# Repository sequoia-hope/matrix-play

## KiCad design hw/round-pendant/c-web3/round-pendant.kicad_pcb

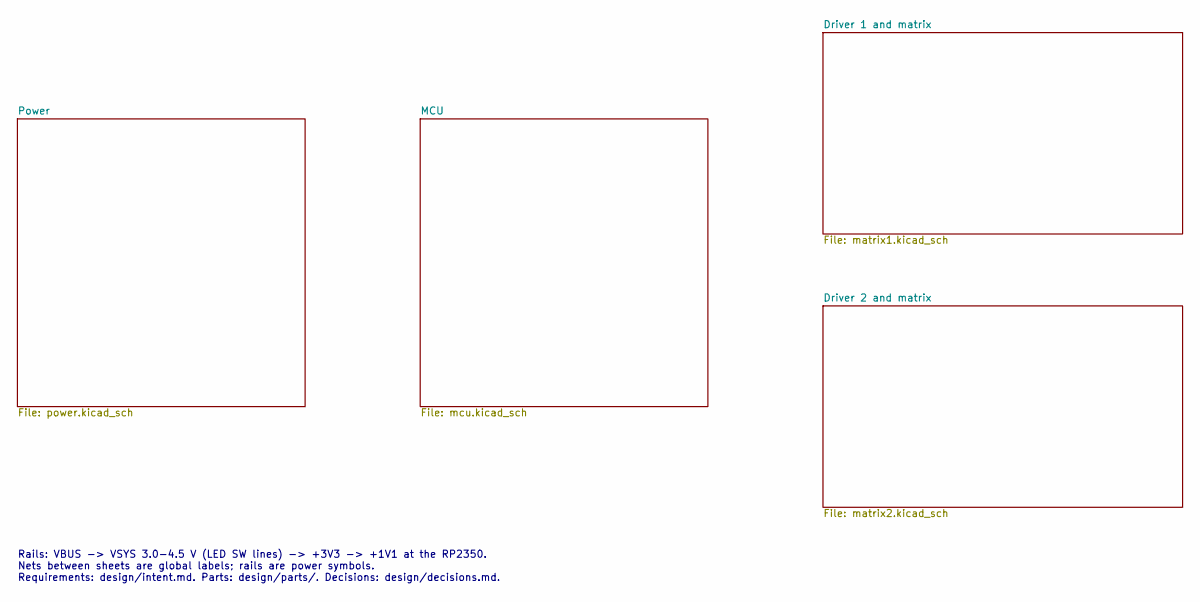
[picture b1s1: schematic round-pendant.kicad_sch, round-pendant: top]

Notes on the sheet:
Rails: VBUS -> VSYS 3.0-4.5 V (LED SW lines) -> +3V3 -> +1V1 at the RP2350. Nets between sheets are global labels; rails are power symbols. Requirements: design/intent.md. Parts: design/parts/. Decisions: design/decisions.md.

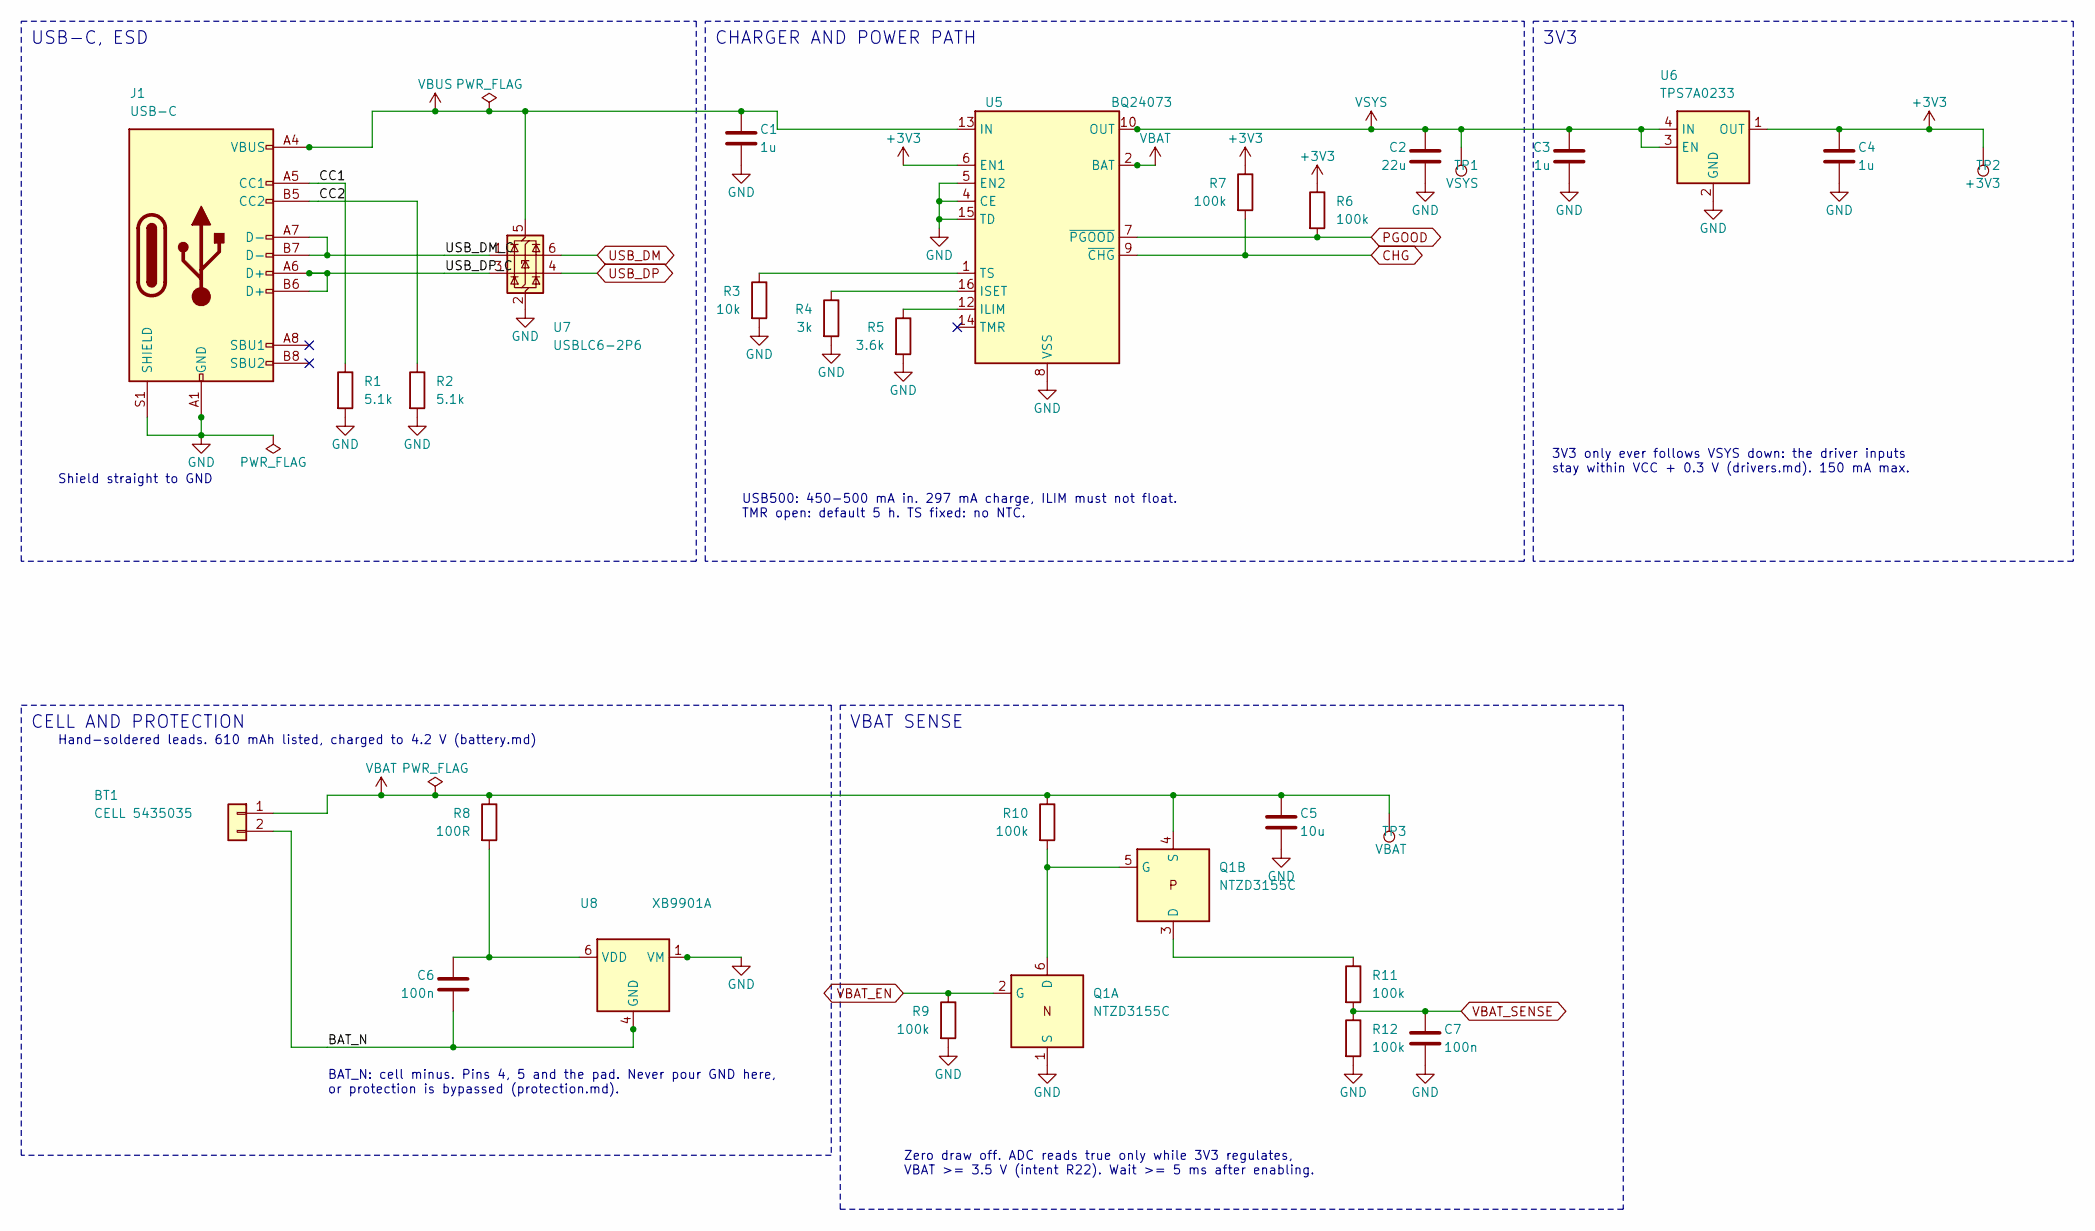
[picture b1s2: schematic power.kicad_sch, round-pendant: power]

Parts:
BT1: CELL 5435035; BatteryPads; MPN 5435035
C1, C3, C4: 1u; C_0402_1005Metric; MPN CL05A105KA5NQNC; LCSC C52923
C2: 22u; C_0603_1608Metric; MPN CL10A226MP8NUNE; LCSC C86295
C5: 10u; C_0603_1608Metric; MPN CL10A106KP8NNNC; LCSC C19702
C6, C7: 100n; C_0402_1005Metric; MPN CL05B104KO5NNNC; LCSC C1525
J1: USB-C; USB_C_Receptacle_HRO_TYPE-C-31-M-12; MPN TYPE-C-31-M-12; LCSC C165948
Q1: NTZD3155C; SOT-563; MPN NTZD3155CT1G; LCSC C236117
R1, R2: 5.1k; R_0402_1005Metric; MPN 0402WGF5101TCE; LCSC C25905
R3: 10k; R_0402_1005Metric; MPN 0402WGF1002TCE; LCSC C25744
R4: 3k; R_0402_1005Metric; MPN 0402WGF3001TCE; LCSC C25784
R5: 3.6k; R_0402_1005Metric; MPN 0402WGF3601TCE; LCSC C25891
R6, R7, R9, R10, R11, R12: 100k; R_0402_1005Metric; MPN 0402WGF1003TCE; LCSC C25741
R8: 100R; R_0402_1005Metric; MPN 0402WGF1000TCE; LCSC C25076
TP1: VSYS; TestPoint_Pad_D1.0mm
TP2: +3V3; TestPoint_Pad_D1.0mm
TP3: VBAT; TestPoint_Pad_D1.0mm
U5: BQ24073; QFN-16-1EP_3x3mm_P0.5mm_EP1.7x1.7mm; MPN BQ24073RGTR; LCSC C15220
U6: TPS7A0233; Texas_X2SON-4_1x1mm_P0.65mm; MPN TPS7A0233PDQNR; LCSC C2860046
U7: USBLC6-2P6; SOT-666; MPN USBLC6-2P6; LCSC C15999
U8: XB9901A; XySemi_DFN-6_1.8x1.4mm; MPN XB9901A; LCSC C669687

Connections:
+3V3: C4.1, R6.1, R7.1, TP2.1, U5.6 (EN1), U6.1 (OUT); also elsewhere on the board
/Power/BAT_N: BT1.2, C6.2, U8.4 (GND), U8.5 (GND)
/Power/CC1: J1.1, J1.A5 (CC1), R1.1
/Power/CC2: J1.2, J1.B5 (CC2), R2.1
/Power/USB_DM_C: J1.3, J1.A7 (D-), J1.B7 (D-), U7.1 (I/O1)
/Power/USB_DP_C: J1.4, J1.A6 (D+), J1.B6 (D+), U7.3 (I/O2)
CHG: R7.2, U5.9 (~CHG); also elsewhere on the board
unnamed: Q1.5 (G), Q1.6 (D), R10.2
unnamed: Q1.3 (D), R11.1
unnamed: R5.1, U5.12 (ILIM)
unnamed: R4.1, U5.16 (ISET)
unnamed: R3.1, U5.1 (TS)
unnamed: C6.1, R8.2, U8.6 (VDD)
PGOOD: R6.2, U5.7 (~PGOOD); also elsewhere on the board
USB_DM: U7.6 (I/O1); also elsewhere on the board
USB_DP: U7.4 (I/O2); also elsewhere on the board
VBAT_EN: Q1.2 (G), R9.1; also elsewhere on the board
VBAT_SENSE: C7.1, R11.2, R12.1; also elsewhere on the board
VSYS: C2.1, C3.1, TP1.1, U5.10 (OUT), U5.11 (OUT), U6.3 (EN), U6.4 (IN); also elsewhere on the board

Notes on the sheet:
Shield straight to GND
USB-C, ESD
USB500: 450-500 mA in. 297 mA charge, ILIM must not float. TMR open: default 5 h. TS fixed: no NTC.
CHARGER AND POWER PATH
3V3 only ever follows VSYS down: the driver inputs stay within VCC + 0.3 V (drivers.md). 150 mA max.
3V3
Hand-soldered leads. 610 mAh listed, charged to 4.2 V (battery.md)
BAT_N: cell minus. Pins 4, 5 and the pad. Never pour GND here, or protection is bypassed (protection.md).
CELL AND PROTECTION
Zero draw off. ADC reads true only while 3V3 regulates, VBAT >= 3.5 V (intent R22). Wait >= 5 ms after enabling.
VBAT SENSE

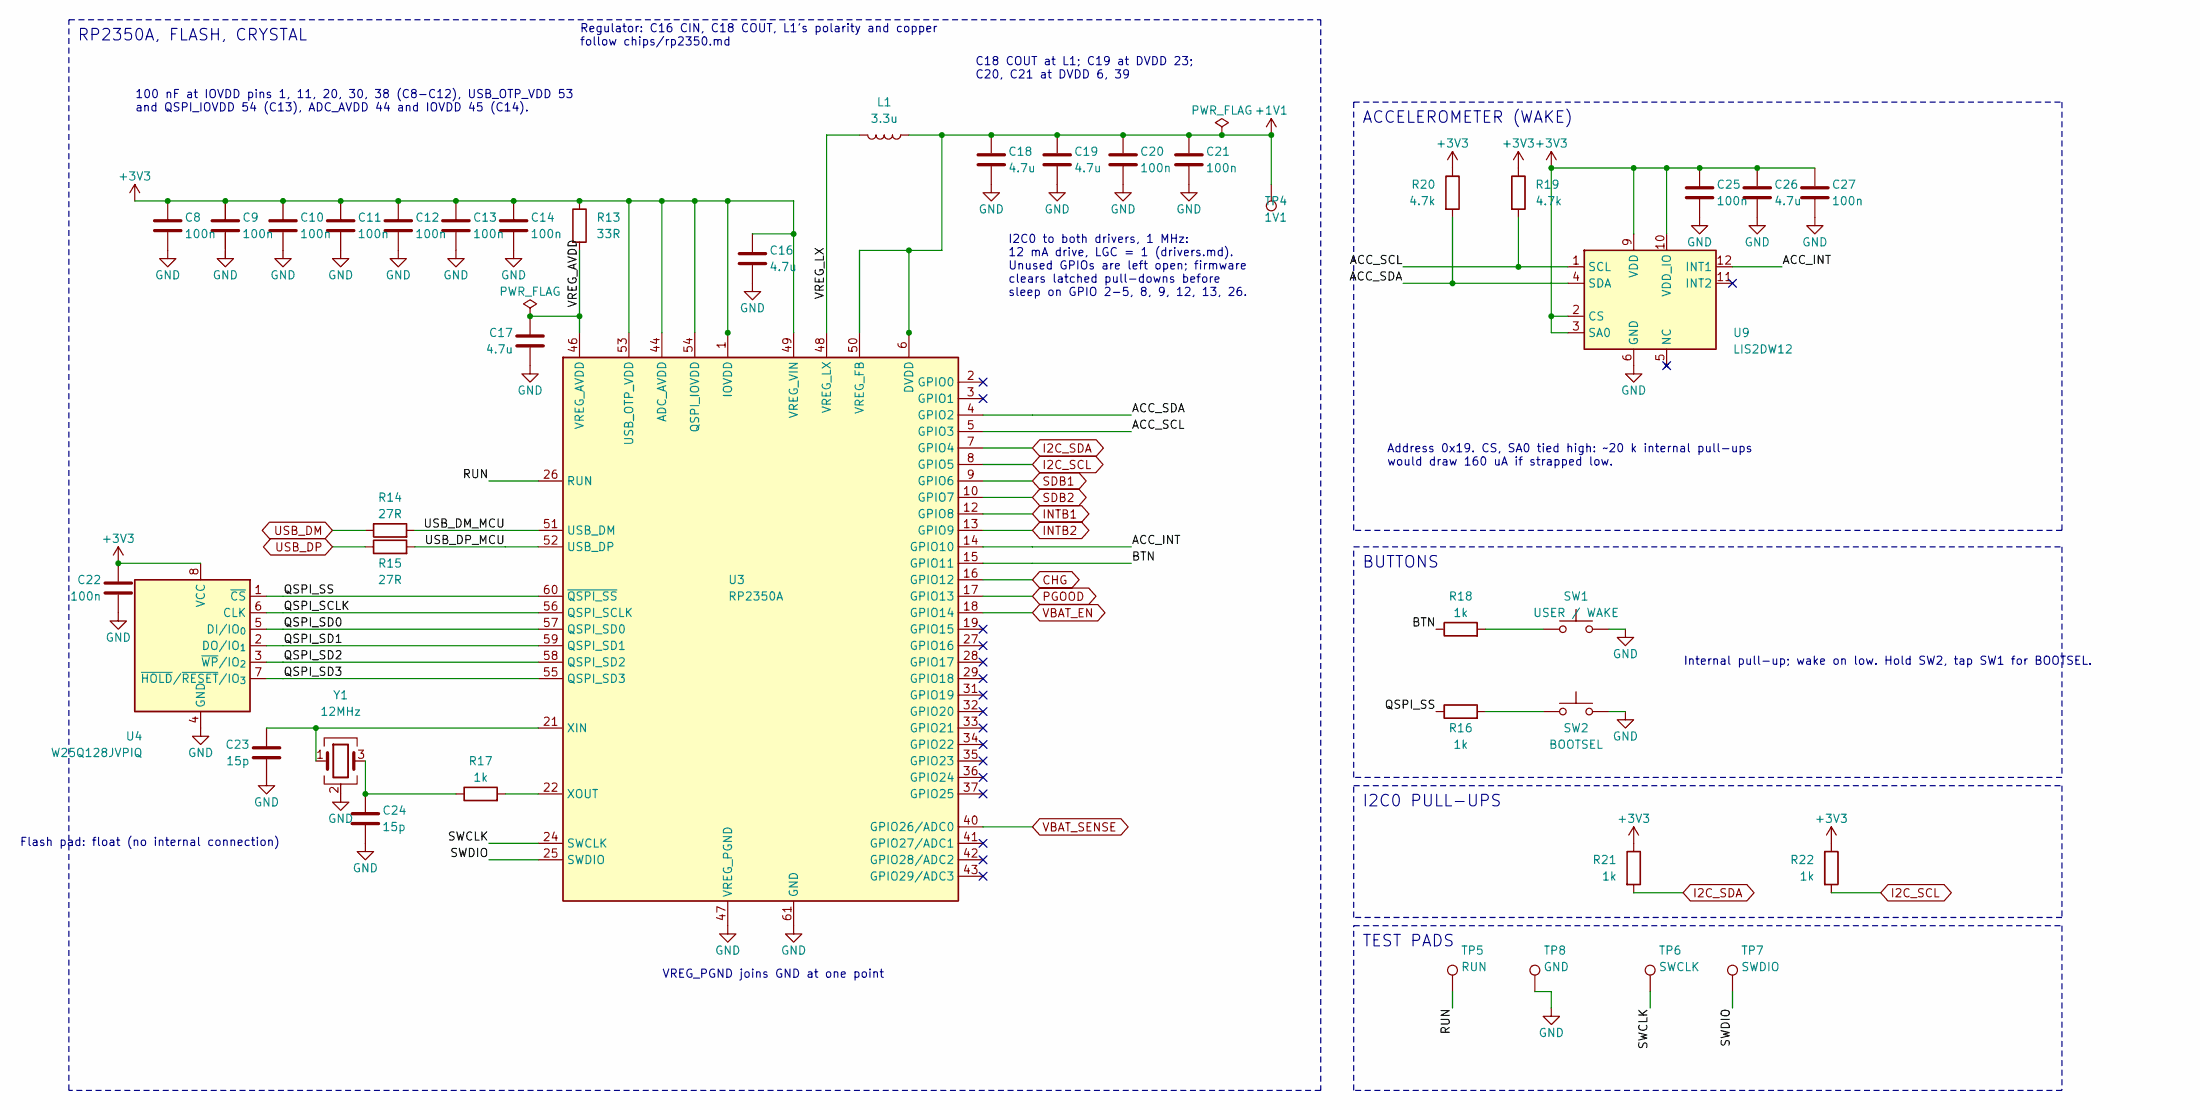
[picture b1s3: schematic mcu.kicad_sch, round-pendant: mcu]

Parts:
C8, C9, C10, C11, C12, C13, C14, C20, C21, C22, C25, C27: 100n; C_0402_1005Metric; MPN CL05B104KO5NNNC; LCSC C1525
C16, C18: 4.7u; C_0402_1005Metric_small_pads; MPN CL05A475MP5NRNC; LCSC C23733
C17, C19, C26: 4.7u; C_0402_1005Metric; MPN CL05A475MP5NRNC; LCSC C23733
C23, C24: 15p; C_0402_1005Metric; MPN 0402CG150J500NT; LCSC C1548
L1: 3.3u; L_pol_2016; MPN AOTA-B201610S3R3-101-T; LCSC C42411119
R13: 33R; R_0402_1005Metric; MPN 0402WGF330JTCE; LCSC C25105
R14, R15: 27R; R_0402_1005Metric; MPN 0402WGF270JTCE; LCSC C25100
R16, R17, R18, R21, R22: 1k; R_0402_1005Metric; MPN 0402WGF1001TCE; LCSC C11702
R19, R20: 4.7k; R_0402_1005Metric; MPN 0402WGF4701TCE; LCSC C25900
SW1: USER / WAKE; SW_Push_1P1T-MP_NO_Horizontal_Alps_SKRTLAE010; MPN SKRTLAE010; LCSC C110293
SW2: BOOTSEL; SW_Push_1P1T-MP_NO_Horizontal_Alps_SKRTLAE010; MPN SKRTLAE010; LCSC C110293
TP4: 1V1; TestPoint_Pad_D1.0mm
TP5: RUN; TestPoint_Pad_D1.0mm
TP6: SWCLK; TestPoint_Pad_D1.0mm
TP7: SWDIO; TestPoint_Pad_D1.0mm
TP8: GND; TestPoint_Pad_D1.0mm
U3: RP2350A; RP2350-QFN-60-1EP_7x7_P0.4mm_EP3.4x3.4mm_ThermalVias; MPN RP2350A; LCSC C42411118
U4: W25Q128JVPIQ; WSON-8_6x5mm_P1.27mm_NoEPCopper; MPN W25Q128JVPIQ; LCSC C190862
U9: LIS2DW12; LGA-12_2x2mm_P0.5mm; MPN LIS2DW12TR; LCSC C189624
Y1: 12MHz; Crystal_SMD_3225-4Pin_3.2x2.5mm; MPN ABM8-272-T3; LCSC C20625731

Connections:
+3V3: C8.1, C9.1, C10.1, C11.1, C12.1, C13.1, C14.1, C16.1, C22.1, C25.1, C26.1, C27.1, R13.1, R19.1, R20.1, R21.1, R22.1, U3.1 (IOVDD), U3.11 (IOVDD), U3.20 (IOVDD), U3.30 (IOVDD), U3.38 (IOVDD), U3.44 (ADC_AVDD), U3.45 (IOVDD), U3.49 (VREG_VIN), U3.53 (USB_OTP_VDD), U3.54 (QSPI_IOVDD), U4.8 (VCC), U9.2 (CS), U9.3 (SA0), U9.9 (VDD), U9.10 (VDD_IO); also elsewhere on the board
/MCU/ACC_INT: U3.14 (GPIO10), U9.12 (INT1)
/MCU/ACC_SCL: R19.2, U3.5 (GPIO3), U9.1 (SCL)
/MCU/ACC_SDA: R20.2, U3.4 (GPIO2), U9.4 (SDA)
/MCU/BTN: R18.1, U3.15 (GPIO11)
/MCU/CLED_B: U3.37 (GPIO25); also elsewhere on the board
/MCU/CLED_G: U3.36 (GPIO24); also elsewhere on the board
/MCU/CLED_R: U3.35 (GPIO23); also elsewhere on the board
/MCU/QSPI_SCLK: U3.56 (QSPI_SCLK), U4.6 (CLK)
/MCU/QSPI_SD0: U3.57 (QSPI_SD0), U4.5 (DI/IO_{0})
/MCU/QSPI_SD1: U3.59 (QSPI_SD1), U4.2 (DO/IO_{1})
/MCU/QSPI_SD2: U3.58 (QSPI_SD2), U4.3 (~WP/IO_{2})
/MCU/QSPI_SD3: U3.55 (QSPI_SD3), U4.7 (~HOLD/~RESET/IO_{3})
/MCU/QSPI_SS: R16.1, U3.60 (~QSPI_SS), U4.1 (~CS)
/MCU/RUN: TP5.1, U3.26 (RUN)
/MCU/SWCLK: TP6.1, U3.24 (SWCLK)
/MCU/SWDIO: TP7.1, U3.25 (SWDIO)
/MCU/USB_DM_MCU: R14.2, U3.51 (USB_DM)
/MCU/USB_DP_MCU: R15.2, U3.52 (USB_DP)
/MCU/VREG_LX: L1.2, U3.48 (VREG_LX)
CHG: U3.16 (GPIO12); also elsewhere on the board
I2C_SCL: R22.2, U3.8 (GPIO5); also elsewhere on the board
I2C_SDA: R21.2, U3.7 (GPIO4); also elsewhere on the board
INTB1: U3.12 (GPIO8); also elsewhere on the board
INTB2: U3.13 (GPIO9); also elsewhere on the board
unnamed: C24.1, R17.1, Y1.3
unnamed: R16.2, SW2.1
unnamed: R18.2, SW1.1
unnamed: C23.1, U3.21 (XIN), Y1.1
unnamed: R17.2, U3.22 (XOUT)
PGOOD: U3.17 (GPIO13); also elsewhere on the board
SDB1: U3.9 (GPIO6); also elsewhere on the board
SDB2: U3.10 (GPIO7); also elsewhere on the board
USB_DM: R14.1; also elsewhere on the board
USB_DP: R15.1; also elsewhere on the board
VBAT_EN: U3.18 (GPIO14); also elsewhere on the board
VBAT_SENSE: U3.40 (GPIO26/ADC0); also elsewhere on the board

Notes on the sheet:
100 nF at IOVDD pins 1, 11, 20, 30, 38 (C8-C12), USB_OTP_VDD 53 and QSPI_IOVDD 54 (C13), ADC_AVDD 44 and IOVDD 45 (C14).
C18 COUT at L1; C19 at DVDD 23; C20, C21 at DVDD 6, 39
Regulator: C16 CIN, C18 COUT, L1's polarity and copper follow chips/rp2350.md
VREG_PGND joins GND at one point
I2C0 to both drivers, 1 MHz: 12 mA drive, LGC = 1 (drivers.md). Unused GPIOs are left open; firmware clears latched pull-downs before sleep on GPIO 2-5, 8, 9, 12, 13, 26.
Flash pad: float (no internal connection)
RP2350A, FLASH, CRYSTAL
Address 0x19. CS, SA0 tied high: ~20 k internal pull-ups would draw 160 uA if strapped low.
ACCELEROMETER (WAKE)
Internal pull-up; wake on low. Hold SW2, tap SW1 for BOOTSEL.
BUTTONS
TEST PADS
I2C0 PULL-UPS

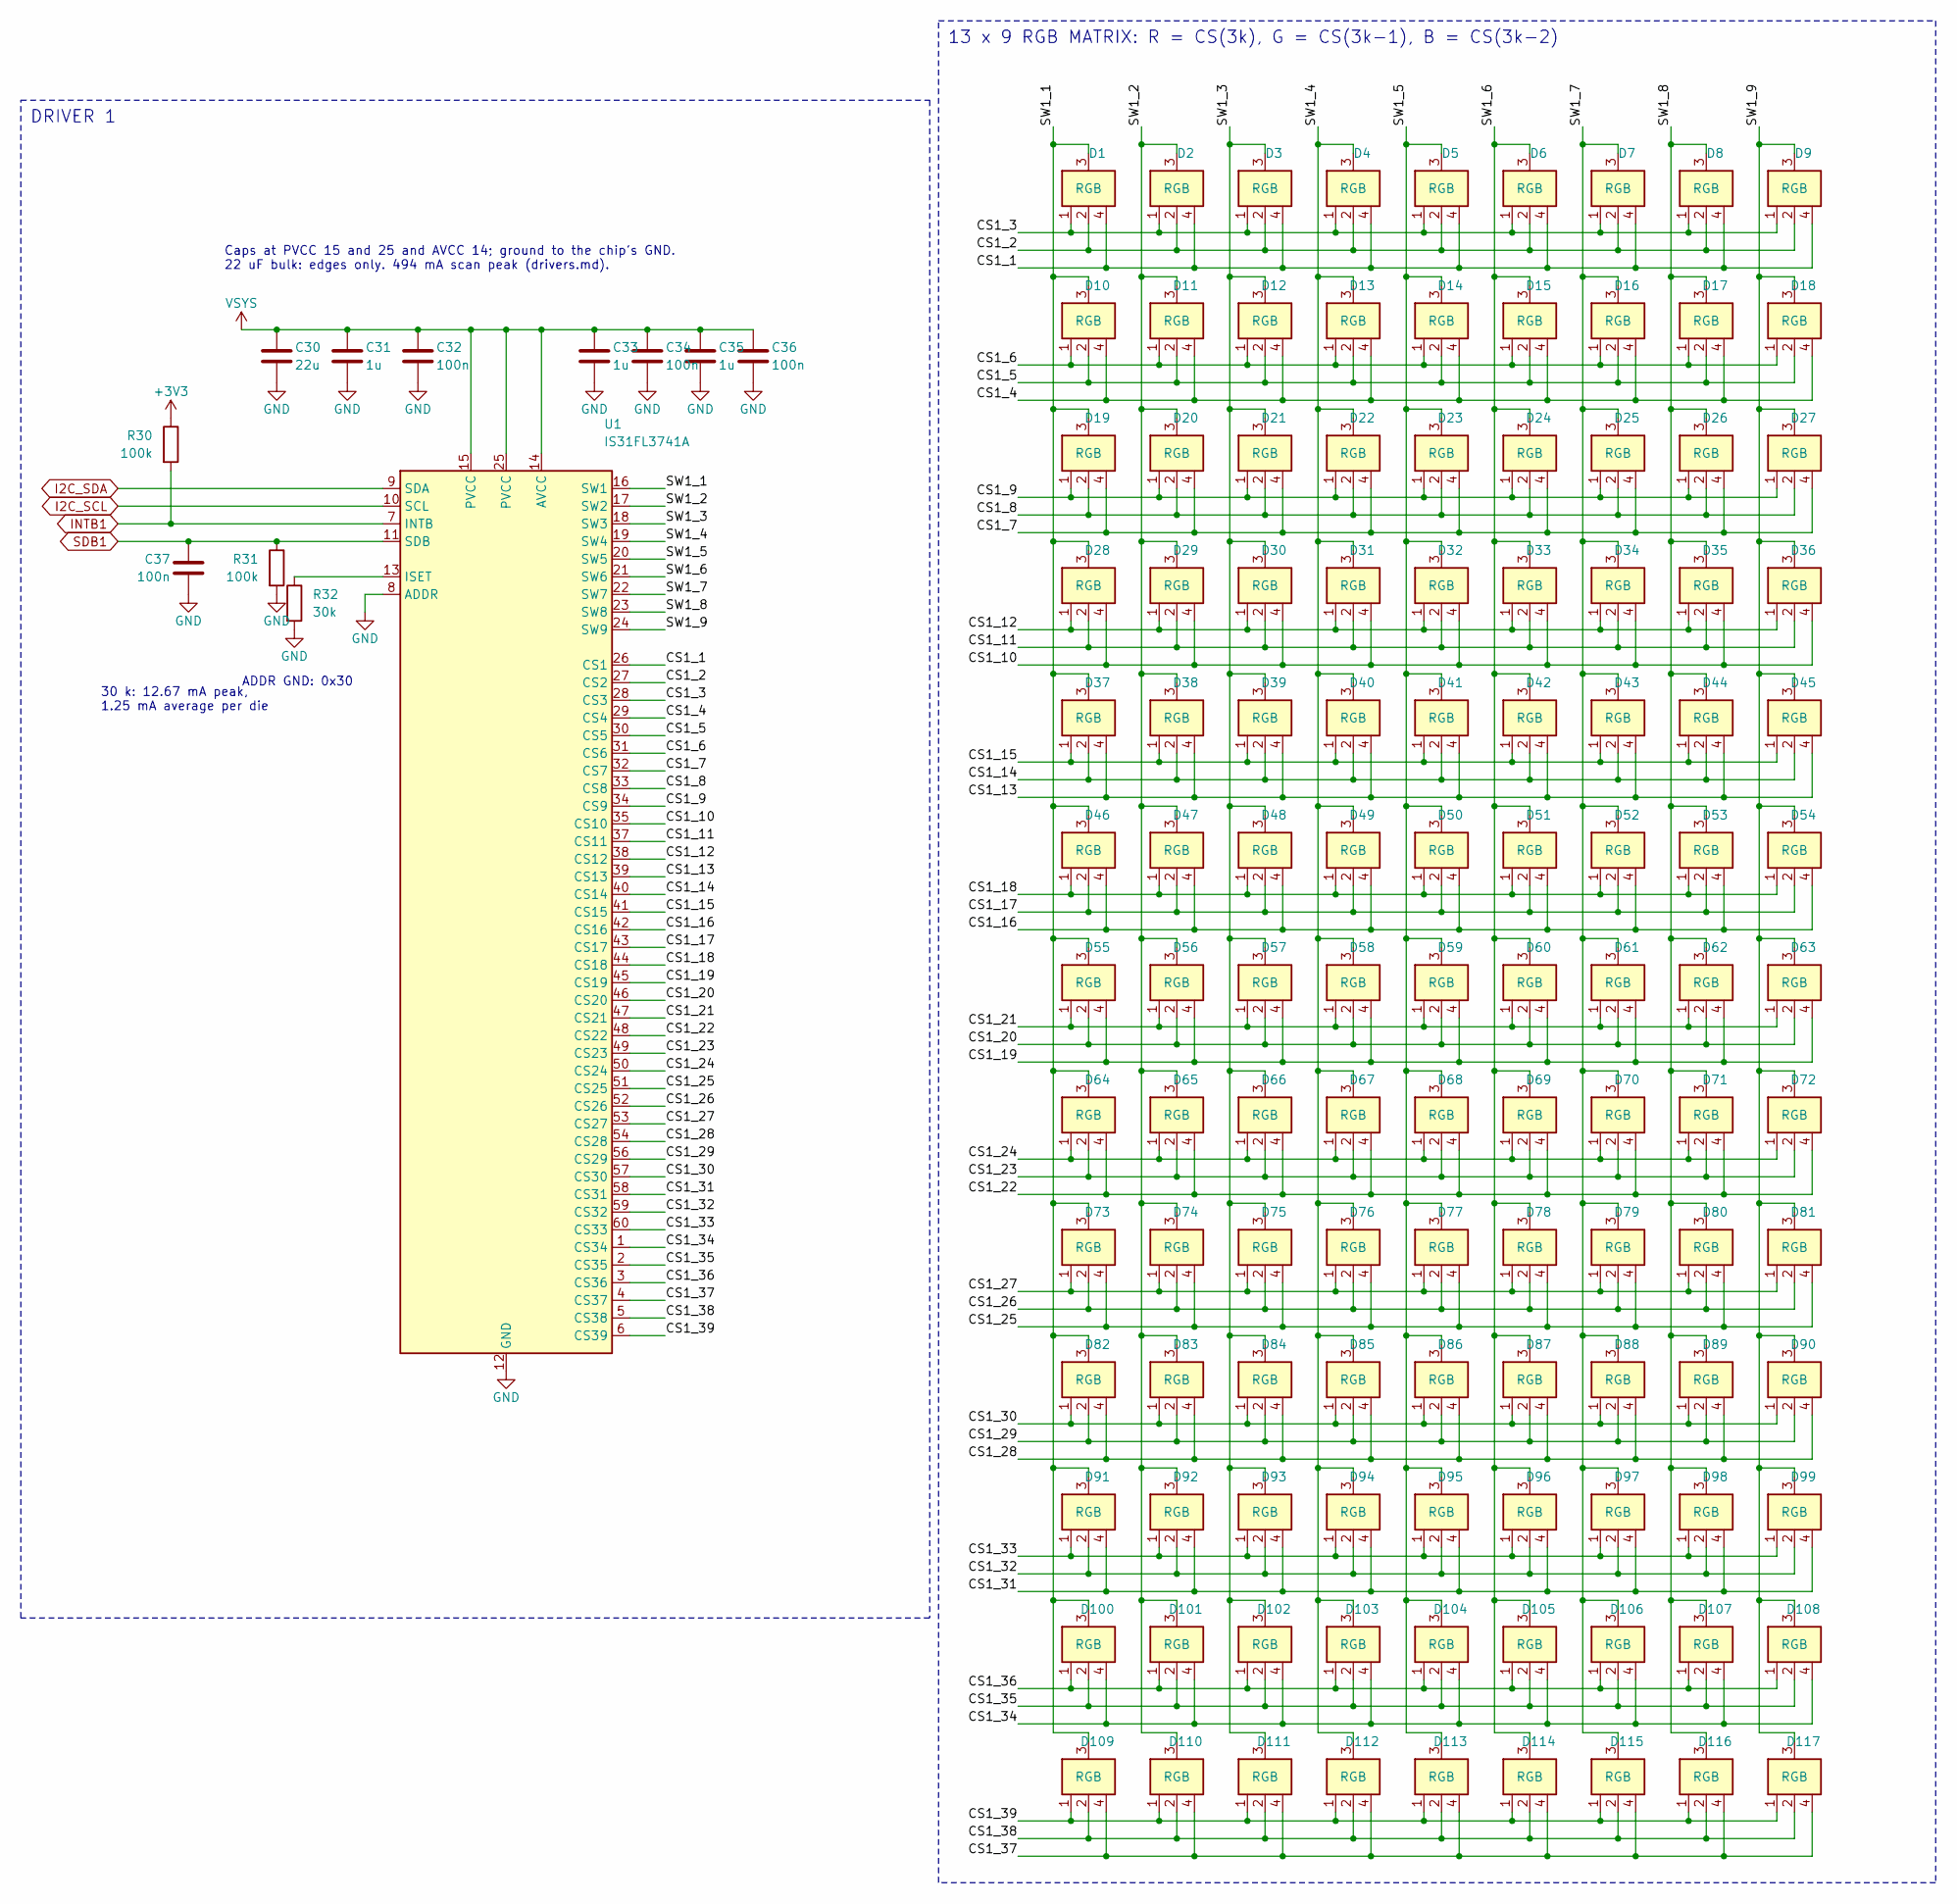
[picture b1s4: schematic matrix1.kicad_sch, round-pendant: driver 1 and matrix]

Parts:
C30: 22u; C_0603_1608Metric; MPN CL10A226MP8NUNE; LCSC C86295
C31, C33, C35: 1u; C_0402_1005Metric; MPN CL05A105KA5NQNC; LCSC C52923
C32, C34, C36, C37: 100n; C_0402_1005Metric; MPN CL05B104KO5NNNC; LCSC C1525
D1, D2, D3, D4, D5, D6, D7, D8, D9, D10, D11, D12, D13, D14, D15, D16, D17, D18, D19, D20, D21, D22, D23, D24, D25, D26, D27, D28, D29, D30, D31, D32, D33, D34, D35, D36, D37, D38, D39, D40, D41, D42, D43, D44, D45, D46, D47, D48, D49, D50, D51, D52, D53, D54, D55, D56, D57, D58, D59, D60, D61, D62, D63, D64, D65, D66, D67, D68, D69, D70, D71, D72, D73, D74, D75, D76, D77, D78, D79, D80, D81, D82, D83, D84, D85, D86, D87, D88, D89, D90, D91, D92, D93, D94, D95, D96, D97, D98, D99, D100, D101, D102, D103, D104, D105, D106, D107, D108, D109, D110, D111, D112, D113, D114, D115, D116, D117: RGB; LED_XL-1010RGB; MPN XL-1010RGB-YG; LCSC C965834
R30, R31: 100k; R_0402_1005Metric; MPN 0402WGF1003TCE; LCSC C25741
R32: 30k; R_0402_1005Metric; MPN 0402WGF3002TCE; LCSC C25776
U1: IS31FL3741A; QFN-60-1EP_7x7mm_P0.4mm_EP5.4x5.4mm; MPN IS31FL3741A-QFLS4-TR; LCSC C2940604

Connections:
+3V3: R30.1; also elsewhere on the board
/Driver 1 and matrix/CS1_1: D1.4 (B), D2.4 (B), D3.4 (B), D4.4 (B), D5.4 (B), D6.4 (B), D7.4 (B), D8.4 (B), D9.4 (B), U1.26 (CS1)
/Driver 1 and matrix/CS1_2: D1.2 (G), D2.2 (G), D3.2 (G), D4.2 (G), D5.2 (G), D6.2 (G), D7.2 (G), D8.2 (G), D9.2 (G), U1.27 (CS2)
/Driver 1 and matrix/CS1_3: D1.1 (R), D2.1 (R), D3.1 (R), D4.1 (R), D5.1 (R), D6.1 (R), D7.1 (R), D8.1 (R), D9.1 (R), U1.28 (CS3)
/Driver 1 and matrix/CS1_4: D10.4 (B), D11.4 (B), D12.4 (B), D13.4 (B), D14.4 (B), D15.4 (B), D16.4 (B), D17.4 (B), D18.4 (B), U1.29 (CS4)
/Driver 1 and matrix/CS1_5: D10.2 (G), D11.2 (G), D12.2 (G), D13.2 (G), D14.2 (G), D15.2 (G), D16.2 (G), D17.2 (G), D18.2 (G), U1.30 (CS5)
/Driver 1 and matrix/CS1_6: D10.1 (R), D11.1 (R), D12.1 (R), D13.1 (R), D14.1 (R), D15.1 (R), D16.1 (R), D17.1 (R), D18.1 (R), U1.31 (CS6)
/Driver 1 and matrix/CS1_7: D19.4 (B), D20.4 (B), D21.4 (B), D22.4 (B), D23.4 (B), D24.4 (B), D25.4 (B), D26.4 (B), D27.4 (B), U1.32 (CS7)
/Driver 1 and matrix/CS1_8: D19.2 (G), D20.2 (G), D21.2 (G), D22.2 (G), D23.2 (G), D24.2 (G), D25.2 (G), D26.2 (G), D27.2 (G), U1.33 (CS8)
/Driver 1 and matrix/CS1_9: D19.1 (R), D20.1 (R), D21.1 (R), D22.1 (R), D23.1 (R), D24.1 (R), D25.1 (R), D26.1 (R), D27.1 (R), U1.34 (CS9)
/Driver 1 and matrix/CS1_10: D28.4 (B), D29.4 (B), D30.4 (B), D31.4 (B), D32.4 (B), D33.4 (B), D34.4 (B), D35.4 (B), D36.4 (B), U1.35 (CS10)
/Driver 1 and matrix/CS1_11: D28.2 (G), D29.2 (G), D30.2 (G), D31.2 (G), D32.2 (G), D33.2 (G), D34.2 (G), D35.2 (G), D36.2 (G), U1.37 (CS11)
/Driver 1 and matrix/CS1_12: D28.1 (R), D29.1 (R), D30.1 (R), D31.1 (R), D32.1 (R), D33.1 (R), D34.1 (R), D35.1 (R), D36.1 (R), U1.38 (CS12)
/Driver 1 and matrix/CS1_13: D37.4 (B), D38.4 (B), D39.4 (B), D40.4 (B), D41.4 (B), D42.4 (B), D43.4 (B), D44.4 (B), D45.4 (B), U1.39 (CS13)
/Driver 1 and matrix/CS1_14: D37.2 (G), D38.2 (G), D39.2 (G), D40.2 (G), D41.2 (G), D42.2 (G), D43.2 (G), D44.2 (G), D45.2 (G), U1.40 (CS14)
/Driver 1 and matrix/CS1_15: D37.1 (R), D38.1 (R), D39.1 (R), D40.1 (R), D41.1 (R), D42.1 (R), D43.1 (R), D44.1 (R), D45.1 (R), U1.41 (CS15)
/Driver 1 and matrix/CS1_16: D46.4 (B), D47.4 (B), D48.4 (B), D49.4 (B), D50.4 (B), D51.4 (B), D52.4 (B), D53.4 (B), D54.4 (B), U1.42 (CS16)
/Driver 1 and matrix/CS1_17: D46.2 (G), D47.2 (G), D48.2 (G), D49.2 (G), D50.2 (G), D51.2 (G), D52.2 (G), D53.2 (G), D54.2 (G), U1.43 (CS17)
/Driver 1 and matrix/CS1_18: D46.1 (R), D47.1 (R), D48.1 (R), D49.1 (R), D50.1 (R), D51.1 (R), D52.1 (R), D53.1 (R), D54.1 (R), U1.44 (CS18)
/Driver 1 and matrix/CS1_19: D55.4 (B), D56.4 (B), D57.4 (B), D58.4 (B), D59.4 (B), D60.4 (B), D61.4 (B), D62.4 (B), D63.4 (B), U1.45 (CS19)
/Driver 1 and matrix/CS1_20: D55.2 (G), D56.2 (G), D57.2 (G), D58.2 (G), D59.2 (G), D60.2 (G), D61.2 (G), D62.2 (G), D63.2 (G), U1.46 (CS20)
/Driver 1 and matrix/CS1_21: D55.1 (R), D56.1 (R), D57.1 (R), D58.1 (R), D59.1 (R), D60.1 (R), D61.1 (R), D62.1 (R), D63.1 (R), U1.47 (CS21)
/Driver 1 and matrix/CS1_22: D64.4 (B), D65.4 (B), D66.4 (B), D67.4 (B), D68.4 (B), D69.4 (B), D70.4 (B), D71.4 (B), D72.4 (B), U1.48 (CS22)
/Driver 1 and matrix/CS1_23: D64.2 (G), D65.2 (G), D66.2 (G), D67.2 (G), D68.2 (G), D69.2 (G), D70.2 (G), D71.2 (G), D72.2 (G), U1.49 (CS23)
/Driver 1 and matrix/CS1_24: D64.1 (R), D65.1 (R), D66.1 (R), D67.1 (R), D68.1 (R), D69.1 (R), D70.1 (R), D71.1 (R), D72.1 (R), U1.50 (CS24)
/Driver 1 and matrix/CS1_25: D73.4 (B), D74.4 (B), D75.4 (B), D76.4 (B), D77.4 (B), D78.4 (B), D79.4 (B), D80.4 (B), D81.4 (B), U1.51 (CS25)
/Driver 1 and matrix/CS1_26: D73.2 (G), D74.2 (G), D75.2 (G), D76.2 (G), D77.2 (G), D78.2 (G), D79.2 (G), D80.2 (G), D81.2 (G), U1.52 (CS26)
/Driver 1 and matrix/CS1_27: D73.1 (R), D74.1 (R), D75.1 (R), D76.1 (R), D77.1 (R), D78.1 (R), D79.1 (R), D80.1 (R), D81.1 (R), U1.53 (CS27)
/Driver 1 and matrix/CS1_28: D82.4 (B), D83.4 (B), D84.4 (B), D85.4 (B), D86.4 (B), D87.4 (B), D88.4 (B), D89.4 (B), D90.4 (B), U1.54 (CS28)
/Driver 1 and matrix/CS1_29: D82.2 (G), D83.2 (G), D84.2 (G), D85.2 (G), D86.2 (G), D87.2 (G), D88.2 (G), D89.2 (G), D90.2 (G), U1.56 (CS29)
/Driver 1 and matrix/CS1_30: D82.1 (R), D83.1 (R), D84.1 (R), D85.1 (R), D86.1 (R), D87.1 (R), D88.1 (R), D89.1 (R), D90.1 (R), U1.57 (CS30)
/Driver 1 and matrix/CS1_31: D91.4 (B), D92.4 (B), D93.4 (B), D94.4 (B), D95.4 (B), D96.4 (B), D97.4 (B), D98.4 (B), D99.4 (B), U1.58 (CS31)
/Driver 1 and matrix/CS1_32: D91.2 (G), D92.2 (G), D93.2 (G), D94.2 (G), D95.2 (G), D96.2 (G), D97.2 (G), D98.2 (G), D99.2 (G), U1.59 (CS32)
/Driver 1 and matrix/CS1_33: D91.1 (R), D92.1 (R), D93.1 (R), D94.1 (R), D95.1 (R), D96.1 (R), D97.1 (R), D98.1 (R), D99.1 (R), U1.60 (CS33)
/Driver 1 and matrix/CS1_34: D100.4 (B), D101.4 (B), D102.4 (B), D103.4 (B), D104.4 (B), D105.4 (B), D106.4 (B), D107.4 (B), D108.4 (B), U1.1 (CS34)
/Driver 1 and matrix/CS1_35: D100.2 (G), D101.2 (G), D102.2 (G), D103.2 (G), D104.2 (G), D105.2 (G), D106.2 (G), D107.2 (G), D108.2 (G), U1.2 (CS35)
/Driver 1 and matrix/CS1_36: D100.1 (R), D101.1 (R), D102.1 (R), D103.1 (R), D104.1 (R), D105.1 (R), D106.1 (R), D107.1 (R), D108.1 (R), U1.3 (CS36)
/Driver 1 and matrix/CS1_37: D109.4 (B), D110.4 (B), D111.4 (B), D112.4 (B), D113.4 (B), D114.4 (B), D115.4 (B), D116.4 (B), D117.4 (B), U1.4 (CS37)
/Driver 1 and matrix/CS1_38: D109.2 (G), D110.2 (G), D111.2 (G), D112.2 (G), D113.2 (G), D114.2 (G), D115.2 (G), D116.2 (G), D117.2 (G), U1.5 (CS38)
/Driver 1 and matrix/CS1_39: D109.1 (R), D110.1 (R), D111.1 (R), D112.1 (R), D113.1 (R), D114.1 (R), D115.1 (R), D116.1 (R), D117.1 (R), U1.6 (CS39)
/Driver 1 and matrix/SW1_1: D1.3 (A), D10.3 (A), D19.3 (A), D28.3 (A), D37.3 (A), D46.3 (A), D55.3 (A), D64.3 (A), D73.3 (A), D82.3 (A), D91.3 (A), D100.3 (A), D109.3 (A), U1.16 (SW1)
/Driver 1 and matrix/SW1_2: D2.3 (A), D11.3 (A), D20.3 (A), D29.3 (A), D38.3 (A), D47.3 (A), D56.3 (A), D65.3 (A), D74.3 (A), D83.3 (A), D92.3 (A), D101.3 (A), D110.3 (A), U1.17 (SW2)
/Driver 1 and matrix/SW1_3: D3.3 (A), D12.3 (A), D21.3 (A), D30.3 (A), D39.3 (A), D48.3 (A), D57.3 (A), D66.3 (A), D75.3 (A), D84.3 (A), D93.3 (A), D102.3 (A), D111.3 (A), U1.18 (SW3)
/Driver 1 and matrix/SW1_4: D4.3 (A), D13.3 (A), D22.3 (A), D31.3 (A), D40.3 (A), D49.3 (A), D58.3 (A), D67.3 (A), D76.3 (A), D85.3 (A), D94.3 (A), D103.3 (A), D112.3 (A), U1.19 (SW4)
/Driver 1 and matrix/SW1_5: D5.3 (A), D14.3 (A), D23.3 (A), D32.3 (A), D41.3 (A), D50.3 (A), D59.3 (A), D68.3 (A), D77.3 (A), D86.3 (A), D95.3 (A), D104.3 (A), D113.3 (A), U1.20 (SW5)
/Driver 1 and matrix/SW1_6: D6.3 (A), D15.3 (A), D24.3 (A), D33.3 (A), D42.3 (A), D51.3 (A), D60.3 (A), D69.3 (A), D78.3 (A), D87.3 (A), D96.3 (A), D105.3 (A), D114.3 (A), U1.21 (SW6)
/Driver 1 and matrix/SW1_7: D7.3 (A), D16.3 (A), D25.3 (A), D34.3 (A), D43.3 (A), D52.3 (A), D61.3 (A), D70.3 (A), D79.3 (A), D88.3 (A), D97.3 (A), D106.3 (A), D115.3 (A), U1.22 (SW7)
/Driver 1 and matrix/SW1_8: D8.3 (A), D17.3 (A), D26.3 (A), D35.3 (A), D44.3 (A), D53.3 (A), D62.3 (A), D71.3 (A), D80.3 (A), D89.3 (A), D98.3 (A), D107.3 (A), D116.3 (A), U1.23 (SW8)
/Driver 1 and matrix/SW1_9: D9.3 (A), D18.3 (A), D27.3 (A), D36.3 (A), D45.3 (A), D54.3 (A), D63.3 (A), D72.3 (A), D81.3 (A), D90.3 (A), D99.3 (A), D108.3 (A), D117.3 (A), U1.24 (SW9)
I2C_SCL: U1.10 (SCL); also elsewhere on the board
I2C_SDA: U1.9 (SDA); also elsewhere on the board
INTB1: R30.2, U1.7 (INTB); also elsewhere on the board
unnamed: R32.1, U1.13 (ISET)
SDB1: C37.1, R31.1, U1.11 (SDB); also elsewhere on the board
VSYS: C30.1, C31.1, C32.1, C33.1, C34.1, C35.1, C36.1, U1.14 (AVCC), U1.15 (PVCC), U1.25 (PVCC); also elsewhere on the board

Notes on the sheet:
Caps at PVCC 15 and 25 and AVCC 14; ground to the chip's GND. 22 uF bulk: edges only. 494 mA scan peak (drivers.md).
ADDR GND: 0x30
30 k: 12.67 mA peak, 1.25 mA average per die
DRIVER 1
13 x 9 RGB MATRIX: R = CS(3k), G = CS(3k-1), B = CS(3k-2)

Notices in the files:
hw/round-pendant/a/matrix1.kicad_sch:
CERN-OHL-P-2.0
